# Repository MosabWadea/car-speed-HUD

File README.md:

# car-speed-HUD
This is a personal project that I am working on. Its aim is to make a heads up display for the speed on the windshield. This repo contains all the hardware and software files that I developed.

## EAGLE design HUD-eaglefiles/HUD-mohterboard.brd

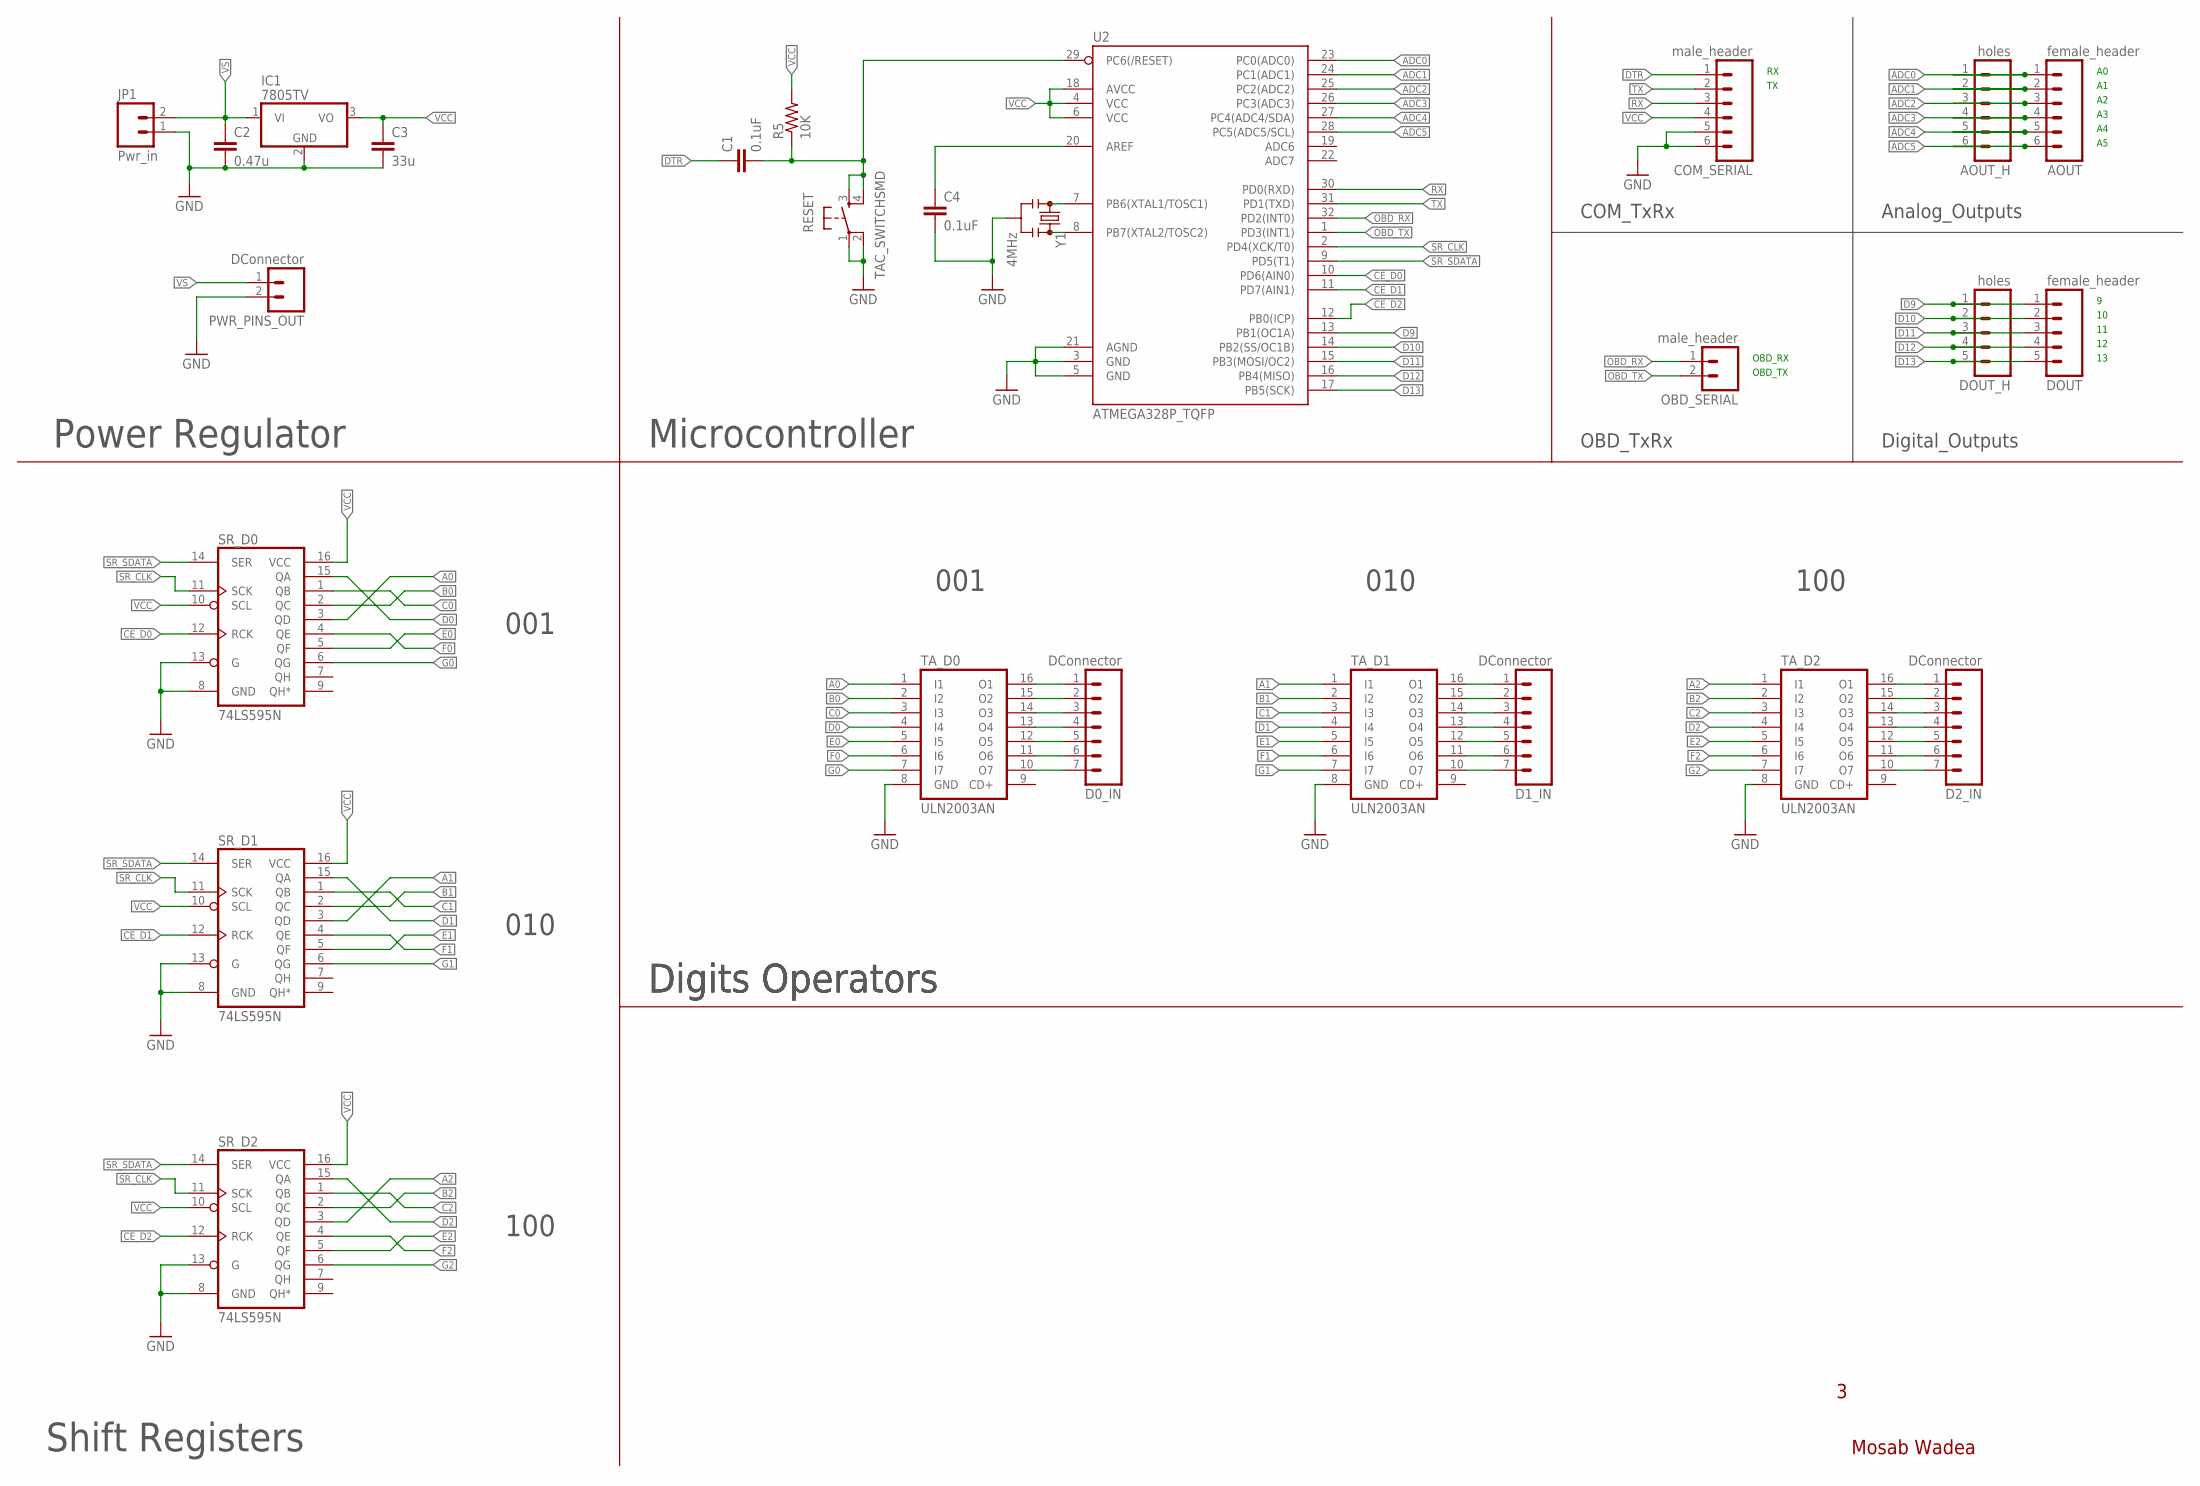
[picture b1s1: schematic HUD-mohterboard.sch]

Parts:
AOUT: female_header; 1X06
AOUT_H: holes; 1X06
C1, C4: 0.1uF; 0805
C2: 0.47u; 0805
C3: 33u; 0805
COM_SERIAL: male_header; 1X06
D0_IN, D1_IN, D2_IN: DConnector; 1X07
DOUT: female_header; 1X05
DOUT_H: holes; 1X05
IC1: 7805TV; TO220V
JP1: Pwr_in; 1X02
OBD_SERIAL: male_header; 1X02
PWR_PINS_OUT: DConnector; 1X02
R5: 10K; 0805
RESET: TAC_SWITCHSMD; TACTILE-SWITCH-SMD
SR_D0, SR_D1, SR_D2: 74LS595N; DIL16
TA_D0, TA_D1, TA_D2: ULN2003AN; DIL16
U2: ATMEGA328P_TQFP; TQFP32-08
Y1: 4MHz; RESONATOR-SMD_MED

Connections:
A0: SR_D0.3 (QD), TA_D0.1 (I1)
A1: SR_D1.3 (QD), TA_D1.1 (I1)
A2: SR_D2.3 (QD), TA_D2.1 (I1)
ADC0: AOUT.1, AOUT_H.1, U2.23 (PC0(ADC0))
ADC1: AOUT.2, AOUT_H.2, U2.24 (PC1(ADC1))
ADC2: AOUT.3, AOUT_H.3, U2.25 (PC2(ADC2))
ADC3: AOUT.4, AOUT_H.4, U2.26 (PC3(ADC3))
ADC4: AOUT.5, AOUT_H.5, U2.27 (PC4(ADC4/SDA))
ADC5: AOUT.6, AOUT_H.6, U2.28 (PC5(ADC5/SCL))
B0: SR_D0.2 (QC), TA_D0.2 (I2)
B1: SR_D1.2 (QC), TA_D1.2 (I2)
B2: SR_D2.2 (QC), TA_D2.2 (I2)
C0: SR_D0.1 (QB), TA_D0.3 (I3)
C1: SR_D1.1 (QB), TA_D1.3 (I3)
C2: SR_D2.1 (QB), TA_D2.3 (I3)
CE_D0: SR_D0.12 (RCK), U2.10 (PD6(AIN0))
CE_D1: SR_D1.12 (RCK), U2.11 (PD7(AIN1))
CE_D2: SR_D2.12 (RCK), U2.12 (PB0(ICP))
D0: SR_D0.15 (QA), TA_D0.4 (I4)
D1: SR_D1.15 (QA), TA_D1.4 (I4)
D2: SR_D2.15 (QA), TA_D2.4 (I4)
D9: DOUT.1, DOUT_H.1, U2.13 (PB1(OC1A))
D10: DOUT.2, DOUT_H.2, U2.14 (PB2(SS/OC1B))
D11: DOUT.3, DOUT_H.3, U2.15 (PB3(MOSI/OC2))
D12: DOUT.4, DOUT_H.4, U2.16 (PB4(MISO))
D13: DOUT.5, DOUT_H.5, U2.17 (PB5(SCK))
DTR: C1.1, COM_SERIAL.1
E0: SR_D0.5 (QF), TA_D0.5 (I5)
E1: SR_D1.5 (QF), TA_D1.5 (I5)
E2: SR_D2.5 (QF), TA_D2.5 (I5)
F0: SR_D0.4 (QE), TA_D0.6 (I6)
F1: SR_D1.4 (QE), TA_D1.6 (I6)
F2: SR_D2.4 (QE), TA_D2.6 (I6)
G0: SR_D0.6 (QG), TA_D0.7 (I7)
G1: SR_D1.6 (QG), TA_D1.7 (I7)
G2: SR_D2.6 (QG), TA_D2.7 (I7)
GND: C2.2, C3.2, C4.2, COM_SERIAL.5, COM_SERIAL.6, IC1.2 (GND), JP1.1, PWR_PINS_OUT.2, RESET.1, RESET.2, SR_D0.8 (GND), SR_D0.13 (G), SR_D1.8 (GND), SR_D1.13 (G), SR_D2.8 (GND), SR_D2.13 (G), TA_D0.8 (GND), TA_D1.8 (GND), TA_D2.8 (GND), U2.3 (GND), U2.5 (GND), U2.21 (AGND), Y1.2
unnamed: U2.7 (PB6(XTAL1/TOSC1)), Y1.1
unnamed: U2.8 (PB7(XTAL2/TOSC2)), Y1.3
unnamed: D0_IN.2, TA_D0.15 (O2)
unnamed: D0_IN.3, TA_D0.14 (O3)
unnamed: D0_IN.4, TA_D0.13 (O4)
unnamed: D0_IN.5, TA_D0.12 (O5)
unnamed: D0_IN.6, TA_D0.11 (O6)
unnamed: D1_IN.3, TA_D1.14 (O3)
unnamed: D1_IN.4, TA_D1.13 (O4)
unnamed: D1_IN.5, TA_D1.12 (O5)
unnamed: D2_IN.4, TA_D2.13 (O4)
unnamed: C4.1, U2.20 (AREF)
unnamed: D1_IN.2, TA_D1.15 (O2)
unnamed: D1_IN.1, TA_D1.16 (O1)
unnamed: D1_IN.6, TA_D1.11 (O6)
unnamed: D1_IN.7, TA_D1.10 (O7)
unnamed: D0_IN.1, TA_D0.16 (O1)
unnamed: D0_IN.7, TA_D0.10 (O7)
unnamed: D2_IN.3, TA_D2.14 (O3)
unnamed: D2_IN.2, TA_D2.15 (O2)
unnamed: D2_IN.1, TA_D2.16 (O1)
unnamed: D2_IN.5, TA_D2.12 (O5)
unnamed: D2_IN.6, TA_D2.11 (O6)
unnamed: D2_IN.7, TA_D2.10 (O7)
OBD_RX: OBD_SERIAL.1, U2.32 (PD2(INT0))
OBD_TX: OBD_SERIAL.2, U2.1 (PD3(INT1))
RESET_WIRE: C1.2, R5.1, RESET.3, RESET.4, U2.29 (PC6(/RESET))
RX: COM_SERIAL.3, U2.30 (PD0(RXD))
SR_CLK: SR_D0.11 (SCK), SR_D1.11 (SCK), SR_D2.11 (SCK), U2.2 (PD4(XCK/T0))
SR_SDATA: SR_D0.14 (SER), SR_D1.14 (SER), SR_D2.14 (SER), U2.9 (PD5(T1))
TX: COM_SERIAL.2, U2.31 (PD1(TXD))
VCC: C3.1, COM_SERIAL.4, IC1.3 (VO), R5.2, SR_D0.10 (SCL), SR_D0.16 (VCC), SR_D1.10 (SCL), SR_D1.16 (VCC), SR_D2.10 (SCL), SR_D2.16 (VCC), U2.4 (VCC), U2.6 (VCC), U2.18 (AVCC)
VS: C2.1, IC1.1 (VI), JP1.2, PWR_PINS_OUT.1

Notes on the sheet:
Mosab Wadea
Power Regulator
Microcontroller
001
010
100
Shift Registers
Digits Operators
OBD_RX
OBD_TX
COM_TxRx
OBD_TxRx
Digital_Outputs
Analog_Outputs

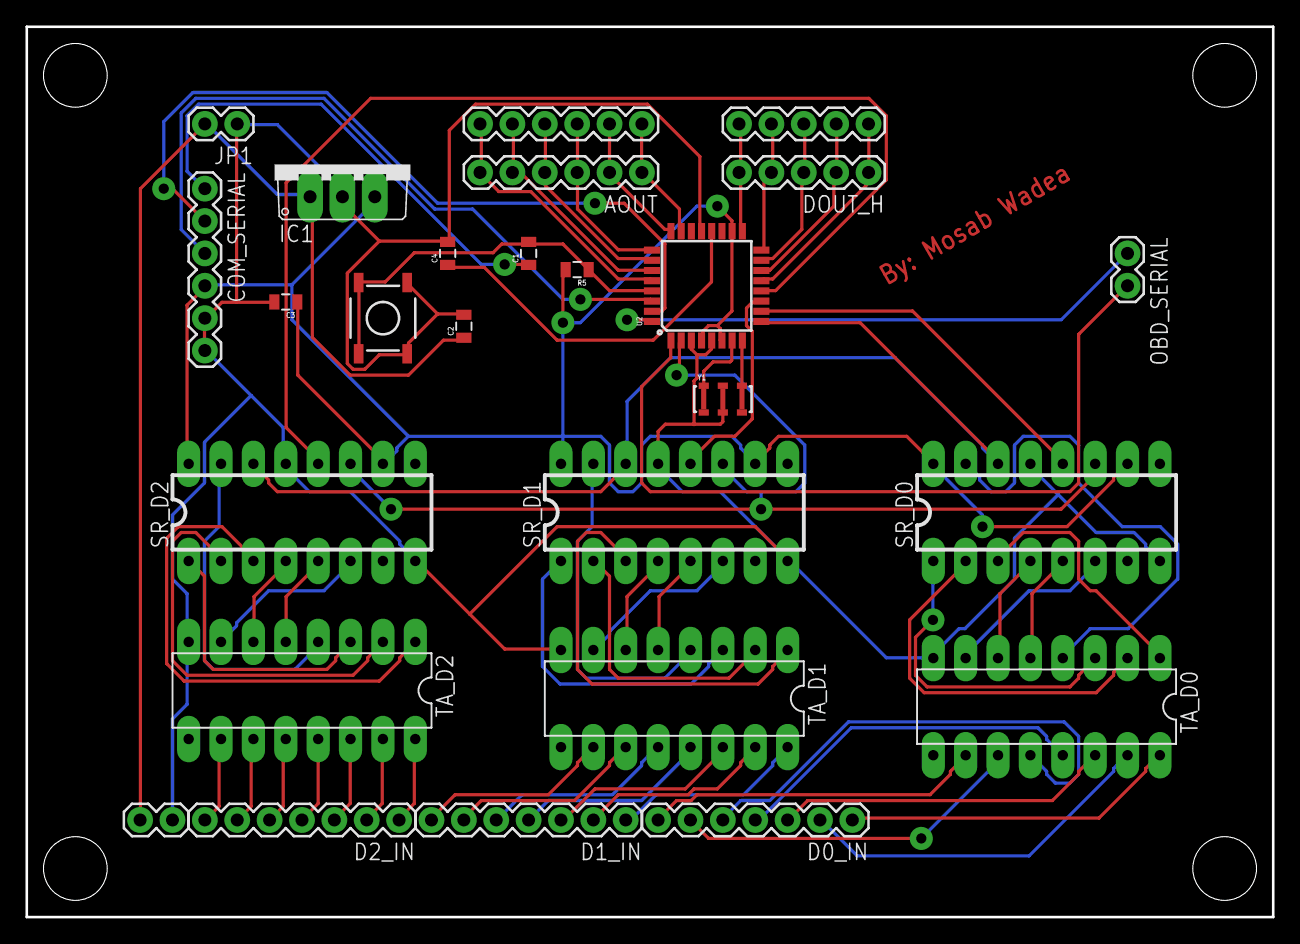
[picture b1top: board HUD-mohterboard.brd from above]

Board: 2 copper layers, 97.8 x 69.8 mm, 26 parts (0 on the bottom side), 70 nets.

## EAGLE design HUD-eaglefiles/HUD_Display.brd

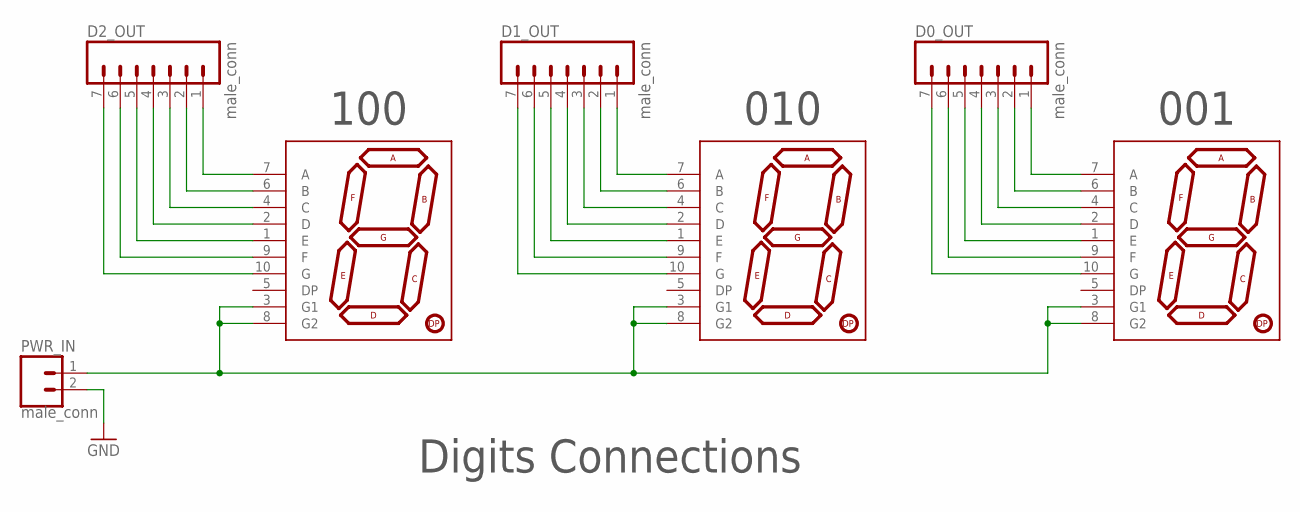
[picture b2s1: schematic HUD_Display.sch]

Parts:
D0, D1, D2: 7-SEGMENT-DISPLAY-1"-REDEZ; 7-SEGMENT-1"PTH-EZ
D0_OUT, D1_OUT, D2_OUT: male_conn; 1X07
PWR_IN: male_conn; 1X02

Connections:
D1_OUT: D1.9 (F), D1_OUT.6
DO_OUT: D2.10 (G), D2_OUT.7
GND: PWR_IN.2
unnamed: D2.7 (A), D2_OUT.1
unnamed: D2.6 (B), D2_OUT.2
unnamed: D2.4 (C), D2_OUT.3
unnamed: D2.2 (D), D2_OUT.4
unnamed: D2.1 (E), D2_OUT.5
unnamed: D2.9 (F), D2_OUT.6
unnamed: D1.7 (A), D1_OUT.1
unnamed: D1.6 (B), D1_OUT.2
unnamed: D1.4 (C), D1_OUT.3
unnamed: D1.2 (D), D1_OUT.4
unnamed: D1.1 (E), D1_OUT.5
unnamed: D1.10 (G), D1_OUT.7
unnamed: D0.7 (A), D0_OUT.1
unnamed: D0.6 (B), D0_OUT.2
unnamed: D0.4 (C), D0_OUT.3
unnamed: D0.2 (D), D0_OUT.4
unnamed: D0.1 (E), D0_OUT.5
unnamed: D0.9 (F), D0_OUT.6
unnamed: D0.10 (G), D0_OUT.7
VCC: D0.3 (G1), D0.8 (G2), D1.3 (G1), D1.8 (G2), D2.3 (G1), D2.8 (G2), PWR_IN.1

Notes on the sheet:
Digits Connections
100
010
001

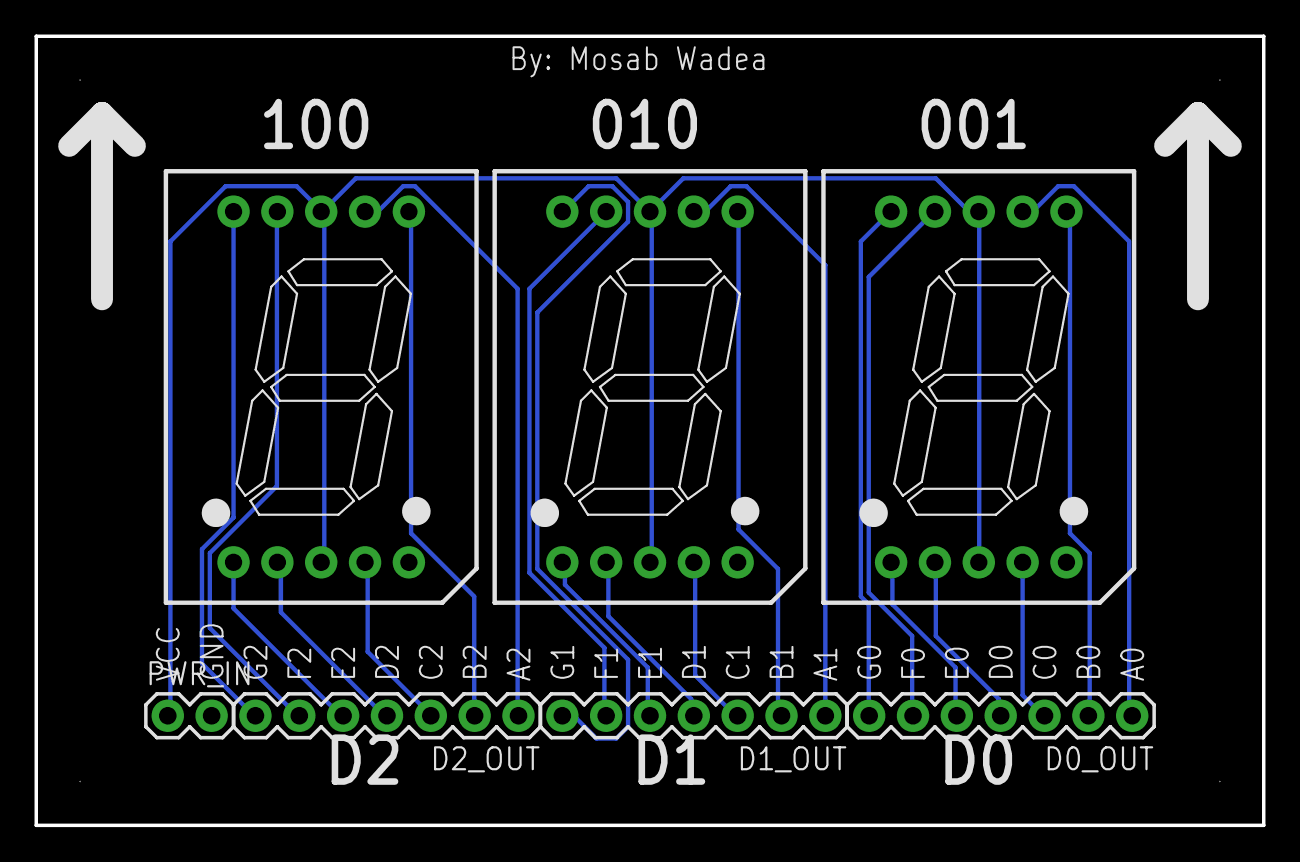
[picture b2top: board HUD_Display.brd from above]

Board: 2 copper layers, 71.1 x 45.7 mm, 7 parts (0 on the bottom side), 22 nets.

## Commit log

2015-06-07 mother board schmatic finished
2015-06-07 added display power output in the motherboard and created the display schematic file
2015-06-07 renamed tranisitors and modified the arrangment, and added valuse for all components
2015-06-07 created initial connections for display
2015-06-07 finilised display cicuit schematic
2015-06-07 renamed the motherboard schematic file
2015-06-07 finalised all circuits and added comments on the motherboard circuit
2015-06-07 arranged the folders
2015-06-07 modified the .ignore file to exclude thunbs.db
2015-06-07 removed the thumbs.db file
2015-06-07 created the display board layout
2015-06-07 modified the shift registers packaging
2015-06-07 startred working on the motherboard layout, and added finale circuit images
2015-06-07 finished the initial matherboard layout and added full layot image
2015-06-07 modified the display layout to make single layer and added the silk screen text
2015-06-07 modified the motherboard layout, fixed output pins arrangment and rerout, and added the silk screen text
2015-06-07 modified the reset button into through hole packaging
2015-06-08 added pdf files that contains the layouts
2015-06-08 added more pdfs
2015-06-08 updated pdfs
2015-11-19 changed the transistors to uln2003 (a transistor array) and rewired the schematic
2015-11-23 added the pins mapping
2015-11-23 fixed the serial port
2015-11-23 new layout for the new schematic
2015-11-23 removed vias from under the mcu
2015-11-23 saved layout pdf and modified bom

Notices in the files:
parts and their libraries:
SparkFun-Connectors: Licensing: Creative Commons ShareAlike 4.0 International - https://creativecommons.org/licenses/by-sa/4.0
